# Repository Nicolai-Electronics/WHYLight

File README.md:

# WHYlight
Hardware design files for the WHYlight project.

A PoE+ powered addressable LED strip driver using an ESP32-C6.

## Features
 - 100mbit ethernet
 - PoE+ powered
 - WiFi / BLE / 802.15.4 radio
 - LoRa radio
 - Suitable for both single and dual wire addressable LEDs
 - TTL differential output for DMX

## License

Copyright 2024 Nicolai Electronics

This project is licensed [CERN-OHL-P](license.txt).

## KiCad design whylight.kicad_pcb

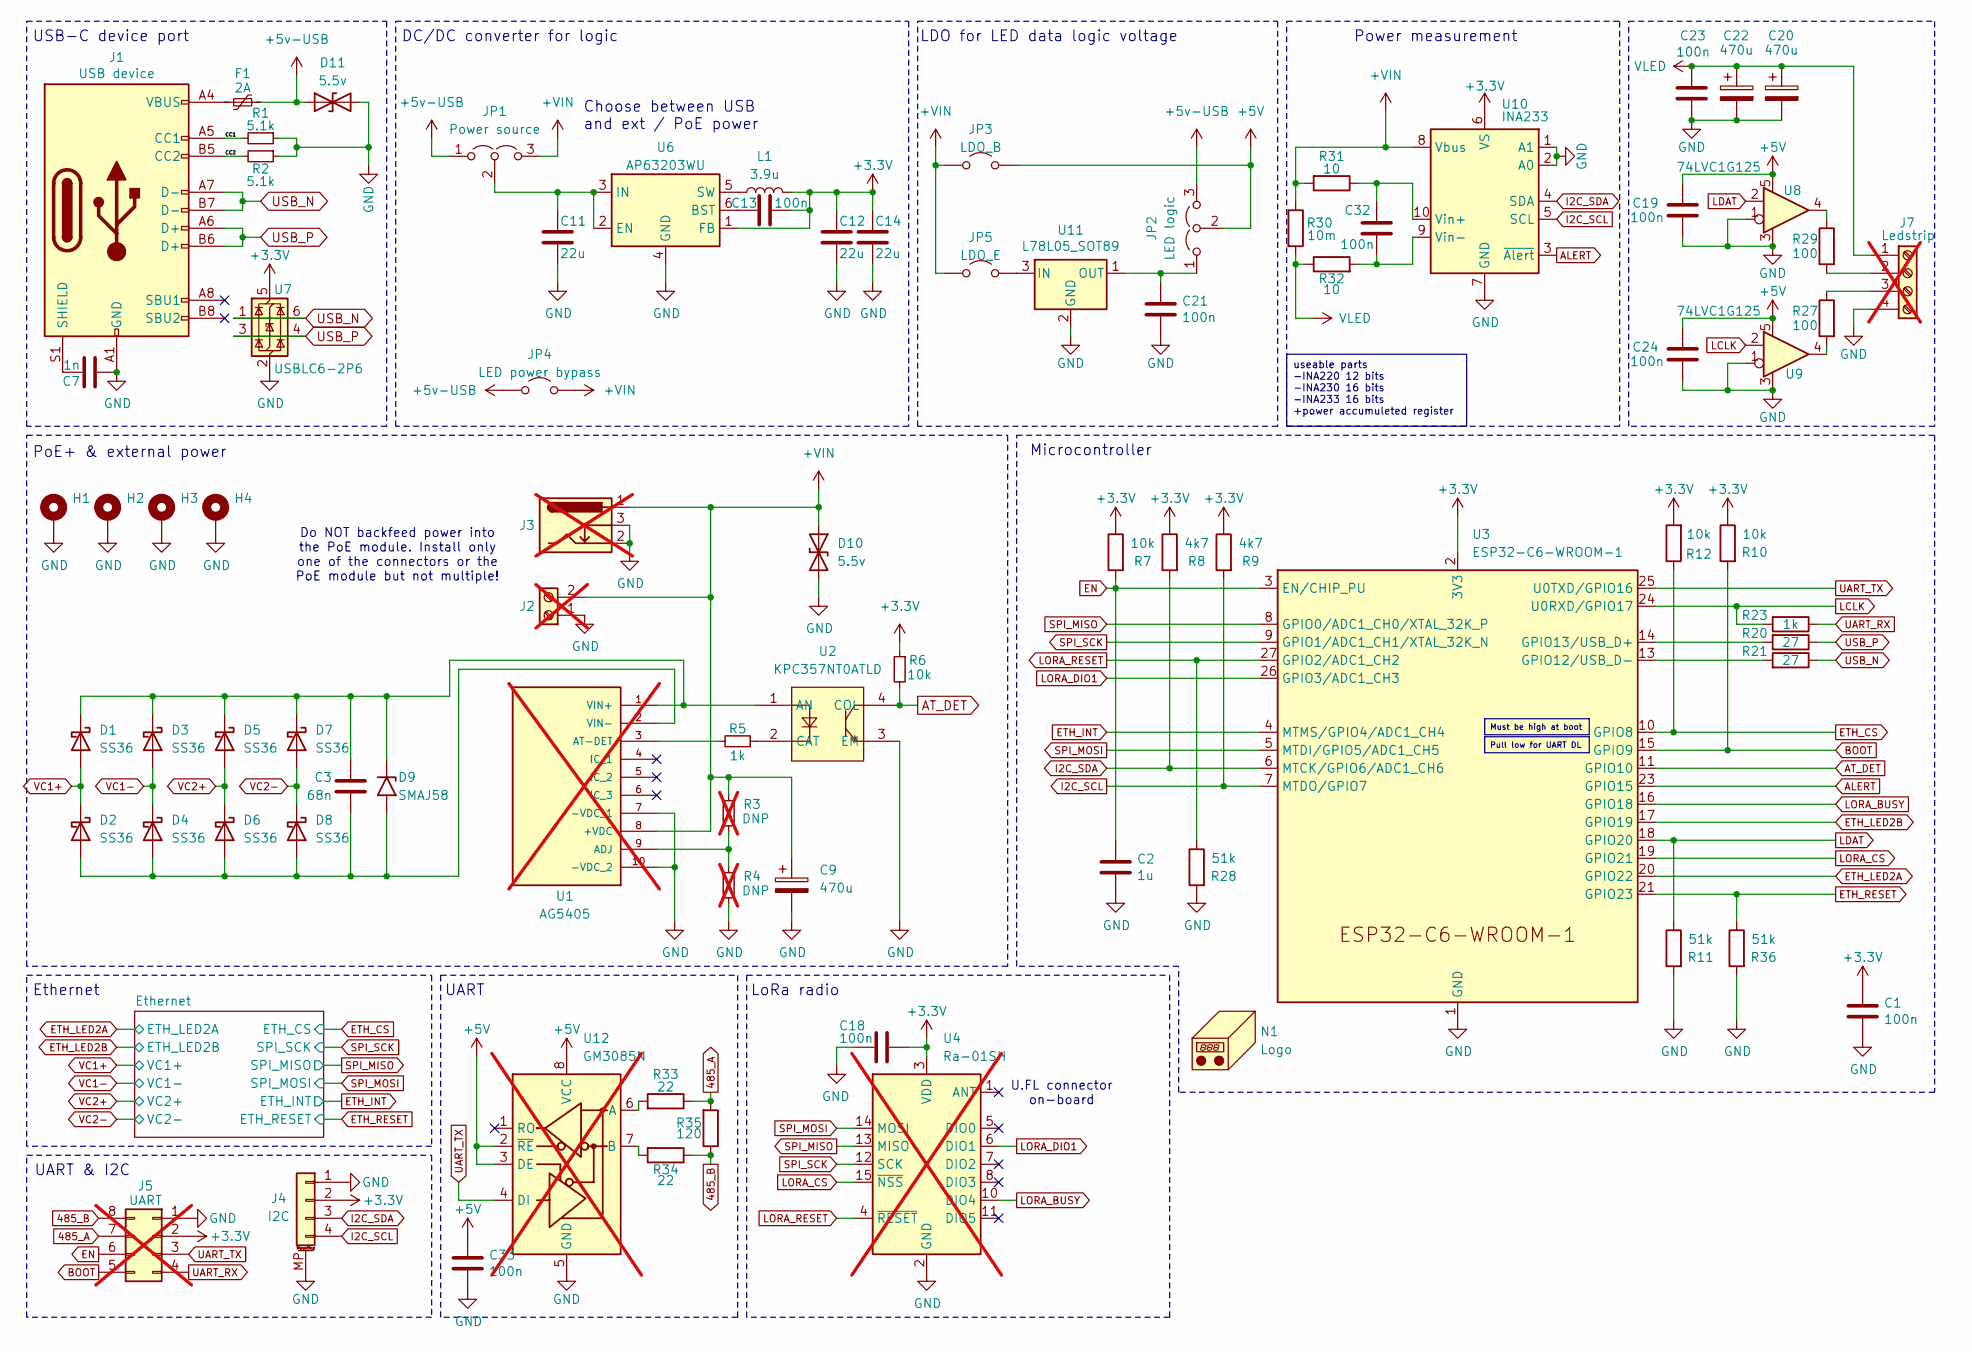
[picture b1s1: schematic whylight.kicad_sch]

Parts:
C1, C13, C18, C19, C21, C23, C24, C32, C33: 100n; C_0402_1005Metric; LCSC C394158
C2: 1u; C_0402_1005Metric; LCSC C5137485
C3: 68n; C_0402_1005Metric; LCSC C565562
C7: 1n; C_1206_3216Metric; LCSC C2173292
C9, C20, C22: 470u; CP_Elec_8x10; LCSC C2164331
C11, C12, C14: 22u; C_0805_2012Metric; LCSC C45783
D1, D2, D3, D4, D5, D6, D7, D8: SS36; D_SMA; LCSC C727061
D9: SMAJ58; D_SMA; LCSC C132935
D10, D11: 5.5v; D_SOD-323; LCSC C19224
F1: 2A; Fuse_0805_2012Metric; LCSC C70158
H1, H2, H3, H4: MountingHole_2.2mm_M2_DIN965_Pad
J1: USB device; USB_C_Receptacle_HRO_TYPE-C-31-M-12; LCSC C165948
J2: External 5v; PhoenixContact_MC_1,5_2-G-5.08_1x02_P5.08mm_Horizontal; LCSC C5188463; not fitted
J3: External 5v; BarrelJack_GCT_DCJ200-10-A_Horizontal; LCSC C381116; not fitted
J4: I2C; JST_SH_BM04B-SRSS-TB_1x04-1MP_P1.00mm_Vertical; LCSC C160390
J5: UART; PinHeader_2x04_P2.54mm_Vertical; not fitted
J7: Ledstrip; PhoenixContact_MC_1,5_4-GF-5.08_1x04_P5.08mm_Horizontal_Thr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; not fitted
JP1: Power source; SolderJumper-3_P1.3mm_Open_RoundedPad1.0x1.5mm_NumberLabels
JP2: LED logic; SolderJumper-3_P1.3mm_Open_RoundedPad1.0x1.5mm_NumberLabels
JP3: LDO_B; SolderJumper-2_P1.3mm_Open_RoundedPad1.0x1.5mm
JP4: LED power bypass; SolderJumper-2_P1.3mm_Open_RoundedPad1.0x1.5mm
JP5: LDO_E; SolderJumper-2_P1.3mm_Open_RoundedPad1.0x1.5mm
L1: 3.9u; L_Coilcraft_XAL5050-XXX; LCSC C167928
N1: Logo; logo_nicolai
R1, R2: 5.1k; R_0402_1005Metric; LCSC C25905
R3, R4: DNP; R_0402_1005Metric; not fitted
R5, R23: 1k; R_0402_1005Metric; LCSC C11702
R6, R7, R10, R12: 10k; R_0402_1005Metric; LCSC C60490
R8, R9: 4k7; R_0402_1005Metric; LCSC C25900
R11, R28, R36: 51k; R_0402_1005Metric; LCSC C25794
R20, R21: 27; R_0402_1005Metric; LCSC C25100
R27, R29: 100; R_0402_1005Metric; LCSC C25076
R30: 10m; R_1206_3216Metric; LCSC C105362
R31, R32: 10; R_0402_1005Metric; LCSC C138066
R33, R34: 22; R_0402_1005Metric; LCSC C25092
R35: 120; R_0402_1005Metric; LCSC C25079
U1: AG5405; AG5300; not fitted
U2: KPC357NT0ATLD; SOP-4_L3.9-W4.4-P2.54-LS7.0-BR; LCSC C136410
U3: ESP32-C6-WROOM-1; LCSC C5366877
U4: Ra-01SH; Ai-Thinker-Ra-01-LoRa; not fitted
U6: AP63203WU; TSOT-23-6; LCSC C780769
U7: USBLC6-2P6; SOT-666; LCSC C2827693
U8, U9: 74LVC1G125; SOT-353_SC-70-5; LCSC C12519
U10: INA233; VSSOP-10_3x3mm_P0.5mm; LCSC C2653838
U11: L78L05_SOT89; SOT-89-3; LCSC C408272
U12: GM3085N; SOIC-8_3.9x4.9mm_P1.27mm; LCSC C269865; not fitted

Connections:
485_A: J5.7, R33.1, R35.2
485_B: J5.8, R34.1, R35.1
+3.3V: C1.1, C12.1, C13.1, C14.1, C18.1, J4.2, J5.2, L1.2, R6.1, R7.1, R8.1, R9.1, R10.1, R12.2, U3.2 (3V3), U4.3 (VDD), U6.1 (FB), U7.5 (VBUS), U10.6 (VS); also elsewhere on the board
+5V: C19.2, C24.2, C33.1, JP2.2 (C), JP3.2 (B), U8.5 (VCC), U9.5 (VCC), U12.2 (~RE), U12.3 (DE), U12.8 (VCC)
+5v-USB: D11.1 (A1), F1.1, JP1.1 (A), JP2.3 (B), JP4.1 (A)
+VIN: C9.1, D10.1 (A1), J2.2, J3.1, JP1.3 (B), JP3.1 (A), JP4.2 (B), JP5.1 (A), R3.2, R30.1, R31.2, U1.8 (+VDC), U10.8 (Vbus)
/CC1: J1.A5 (CC1), R1.2
/CC2: J1.B5 (CC2), R2.2
ALERT: U3.23 (GPIO15), U10.3 (~Alert)
AT_DET: R6.2, U2.4 (COL), U3.11 (GPIO10)
BOOT: J5.5, R10.2, U3.15 (GPIO9)
EN: C2.1, J5.6, R7.2, U3.3 (EN/CHIP_PU)
ETH_CS: R12.1, U3.10 (GPIO8); also elsewhere on the board
ETH_INT: U3.4 (MTMS/GPIO4/ADC1_CH4); also elsewhere on the board
ETH_LED2A: U3.20 (GPIO22); also elsewhere on the board
ETH_LED2B: U3.17 (GPIO19); also elsewhere on the board
ETH_RESET: R36.1, U3.21 (GPIO23); also elsewhere on the board
GND: C1.2, C2.2, C7.2, C9.2, C11.2, C12.2, C14.2, C18.2, C19.1, C20.2, C21.2, C22.2, C23.2, C24.1, C33.2, D10.2 (A2), D11.2 (A2), H1.1, H2.1, H3.1, H4.1, J1.A1 (GND), J1.A12 (GND), J1.B1 (GND), J1.B12 (GND), J2.1, J3.2, J3.3, J4.1, J4.MP (MountPin), J5.1, J7.4, R1.1, R2.1, R4.1, R11.2, R28.2, R36.2, U1.7 (-VDC_1), U1.10 (-VDC_2), U2.3 (EM), U3.1 (GND), U3.12 (GPIO11), U3.28 (GND), U3.29 (GND), U4.2 (GND), U4.9 (GND), U4.16 (GND), U6.4 (GND), U7.2 (GND), U8.1, U8.3 (GND), U9.1, U9.3 (GND), U10.1 (A1), U10.2 (A0), U10.7 (GND), U11.2 (GND), U12.5 (GND); also elsewhere on the board
I2C_SCL: J4.4, R9.2, U3.7 (MTDO/GPIO7), U10.5 (SCL)
I2C_SDA: J4.3, R8.2, U3.6 (MTCK/GPIO6/ADC1_CH6), U10.4 (SDA)
LCLK: R23.2, U3.24 (U0RXD/GPIO17), U9.2
LDAT: R11.1, U3.18 (GPIO20), U8.2
LORA_BUSY: U3.16 (GPIO18), U4.10 (DIO4)
LORA_CS: U3.19 (GPIO21), U4.15 (~NSS)
LORA_DIO1: U3.26 (GPIO3/ADC1_CH3), U4.6 (DIO1)
LORA_RESET: R28.1, U3.27 (GPIO2/ADC1_CH2), U4.4 (~RESET)
unnamed: C3.1, D1.1 (K), D3.1 (K), D5.1 (K), D7.1 (K), D9.1 (A1), U1.1 (VIN+), U2.1 (AN)
unnamed: C3.2, D2.2 (A), D4.2 (A), D6.2 (A), D8.2 (A), D9.2 (A2), U1.2 (VIN-)
unnamed: F1.2, J1.A4 (VBUS), J1.A9 (VBUS), J1.B4 (VBUS), J1.B9 (VBUS)
unnamed: C7.1, J1.S1 (SHIELD)
unnamed: J7.2, R29.2
unnamed: J7.3, R27.1
unnamed: C11.1, JP1.2 (C), U6.2 (EN), U6.3 (IN)
unnamed: C21.1, JP2.1 (A), U11.1 (OUT)
unnamed: JP5.2 (B), U11.3 (IN)
unnamed: R27.2, U9.4
unnamed: R29.1, U8.4
unnamed: R3.1, R4.2, U1.9 (ADJ)
unnamed: R5.2, U1.3 (AT-DET)
unnamed: R5.1, U2.2 (CAT)
unnamed: R21.2, U3.13 (GPIO12/USB_D-)
unnamed: R20.2, U3.14 (GPIO13/USB_D+)
unnamed: C13.2, U6.6 (BST)
unnamed: L1.1, U6.5 (SW)
unnamed: C32.2, R31.1, U10.10 (Vin+)
unnamed: C32.1, R32.2, U10.9 (Vin-)
unnamed: R33.2, U12.6 (A)
unnamed: R34.2, U12.7 (B)
SPI_MISO: U3.8 (GPIO0/ADC1_CH0/XTAL_32K_P), U4.13 (MISO); also elsewhere on the board
SPI_MOSI: U3.5 (MTDI/GPIO5/ADC1_CH5), U4.14 (MOSI); also elsewhere on the board
SPI_SCK: U3.9 (GPIO1/ADC1_CH1/XTAL_32K_N), U4.12 (SCK); also elsewhere on the board
UART_RX: J5.4, R23.1
UART_TX: J5.3, U3.25 (U0TXD/GPIO16), U12.4 (DI)
USB_N: J1.A7 (D-), J1.B7 (D-), R21.1, U7.1 (I/O1), U7.6 (I/O1)
USB_P: J1.A6 (D+), J1.B6 (D+), R20.1, U7.3 (I/O2), U7.4 (I/O2)
VC1+: D1.2 (A), D2.1 (K); also elsewhere on the board
VC1-: D3.2 (A), D4.1 (K); also elsewhere on the board
VC2+: D5.2 (A), D6.1 (K); also elsewhere on the board
VC2-: D7.2 (A), D8.1 (K); also elsewhere on the board
VLED: C20.1, C22.1, C23.1, J7.1, R30.2, R32.1

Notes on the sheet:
Pull low for UART DL
Must be high at boot
useable parts -INA220 12 bits -INA230 16 bits -INA233 16 bits +power accumuleted register
Ethernet
Choose between USB and ext / PoE power
USB-C device port
Microcontroller
Power measurement
UART
DC/DC converter for logic
U.FL connector on-board
LoRa radio
PoE+ & external power
LDO for LED data logic voltage
UART & I2C
Do NOT backfeed power into the PoE module. Install only one of the connectors or the PoE module but not multiple!

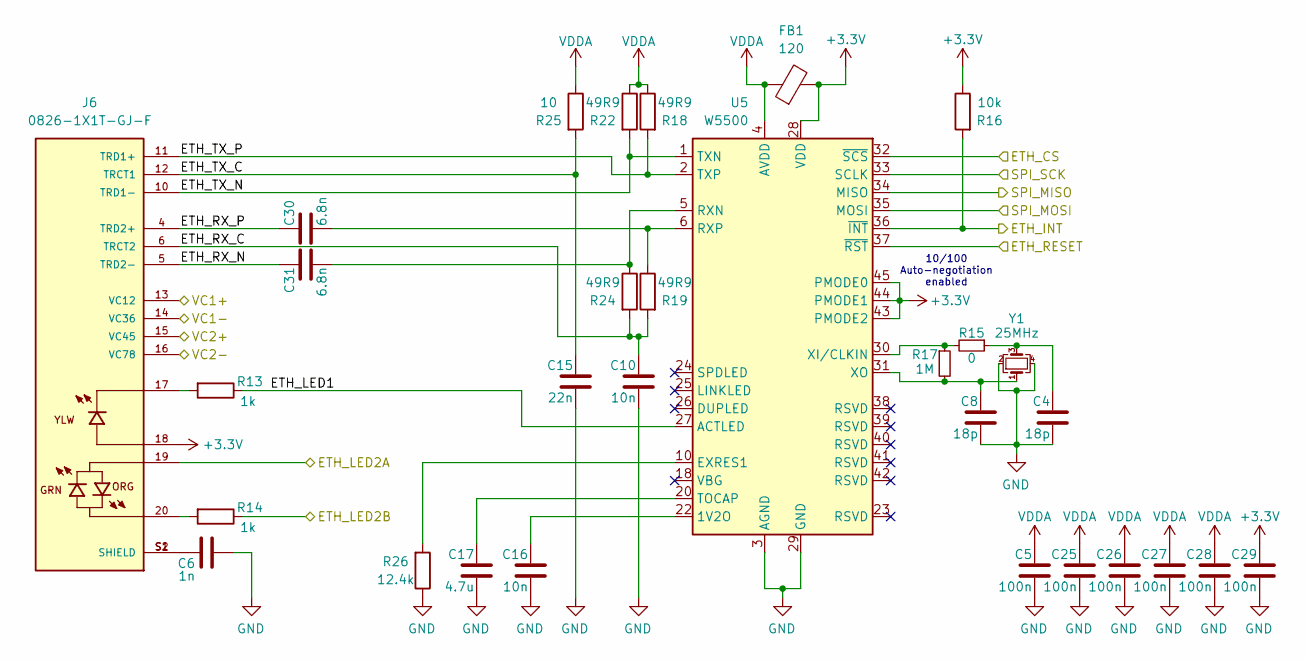
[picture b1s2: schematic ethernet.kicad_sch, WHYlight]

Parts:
C4, C8: 18p; C_0402_1005Metric; LCSC C555395
C5, C25, C26, C27, C28, C29: 100n; C_0402_1005Metric; LCSC C394158
C6: 1n; C_1206_3216Metric; LCSC C2173292
C10, C16: 10n; C_0402_1005Metric; LCSC C2875126
C15: 22n; C_0402_1005Metric; LCSC C466237
C17: 4.7u; C_0402_1005Metric; LCSC C307423
C30, C31: 6.8n; C_0402_1005Metric; LCSC C2760541
FB1: 120; L_0603_1608Metric; LCSC C709642
J6: 0826-1X1T-GJ-F; BEL_0826-1X1T-GJ-F
R13, R14: 1k; R_0402_1005Metric; LCSC C11702
R15: 0; R_0402_1005Metric; LCSC C17168
R16: 10k; R_0402_1005Metric; LCSC C60490
R17: 1M; R_0402_1005Metric; LCSC C26083
R18, R19, R22, R24: 49R9; R_0402_1005Metric; LCSC C25120
R25: 10; R_0402_1005Metric; LCSC C138066
R26: 12.4k; R_0402_1005Metric; LCSC C284314
U5: W5500; LQFP-48_7x7mm_P0.5mm; LCSC C32843
Y1: 25MHz; Crystal_SMD_3225-4Pin_3.2x2.5mm; LCSC C7424735

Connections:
+3.3V: C29.1, FB1.2, J6.18, R16.1, U5.28 (VDD), U5.43 (PMODE2), U5.44 (PMODE1), U5.45 (PMODE0); also elsewhere on the board
/Ethernet/ETH_LED1: R13.1, U5.27 (ACTLED)
/Ethernet/ETH_RX_C: C10.1, J6.6 (TRCT2), R19.2, R24.2
/Ethernet/ETH_RX_N: C31.1, J6.5 (TRD2-)
/Ethernet/ETH_RX_P: C30.1, J6.4 (TRD2+)
/Ethernet/ETH_TX_C: C15.1, J6.12 (TRCT1), R25.2
/Ethernet/ETH_TX_N: J6.10 (TRD1-), R22.2, U5.1 (TXN)
/Ethernet/ETH_TX_P: J6.11 (TRD1+), R18.2, U5.2 (TXP)
ETH_CS: U5.32 (~SCS); also elsewhere on the board
ETH_INT: R16.2, U5.36 (~INT); also elsewhere on the board
ETH_LED2A: J6.19; also elsewhere on the board
ETH_LED2B: R14.1; also elsewhere on the board
ETH_RESET: U5.37 (~RST); also elsewhere on the board
GND: C4.2, C5.2, C6.2, C8.2, C10.2, C15.2, C16.2, C17.2, C25.2, C26.2, C27.2, C28.2, C29.2, R26.1, U5.3 (AGND), U5.9 (AGND), U5.14 (AGND), U5.16 (AGND), U5.19 (AGND), U5.29 (GND), U5.48 (AGND), Y1.2, Y1.4; also elsewhere on the board
unnamed: C4.1, R15.1, Y1.3
unnamed: C6.1, J6.S1 (SHIELD), J6.S2 (SHIELD)
unnamed: J6.17, R13.2
unnamed: J6.20, R14.2
unnamed: C16.1, U5.22 (1V2O)
unnamed: R26.2, U5.10 (EXRES1)
unnamed: C31.2, R24.1, U5.5 (RXN)
unnamed: C30.2, R19.1, U5.6 (RXP)
unnamed: C17.1, U5.20 (TOCAP)
unnamed: R15.2, R17.1, U5.30 (XI/CLKIN)
unnamed: C8.1, R17.2, U5.31 (XO), Y1.1
SPI_MISO: U5.34 (MISO); also elsewhere on the board
SPI_MOSI: U5.35 (MOSI); also elsewhere on the board
SPI_SCK: U5.33 (SCLK); also elsewhere on the board
VC1+: J6.13 (VC12); also elsewhere on the board
VC1-: J6.14 (VC36); also elsewhere on the board
VC2+: J6.15 (VC45); also elsewhere on the board
VC2-: J6.16 (VC78); also elsewhere on the board
VDDA: C5.1, C25.1, C26.1, C27.1, C28.1, FB1.1, R18.1, R22.1, R25.1, U5.4 (AVDD), U5.8 (AVDD), U5.11 (AVDD), U5.15 (AVDD), U5.17 (AVDD), U5.21 (AVDD)

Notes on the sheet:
10/100 Auto-negotiation enabled

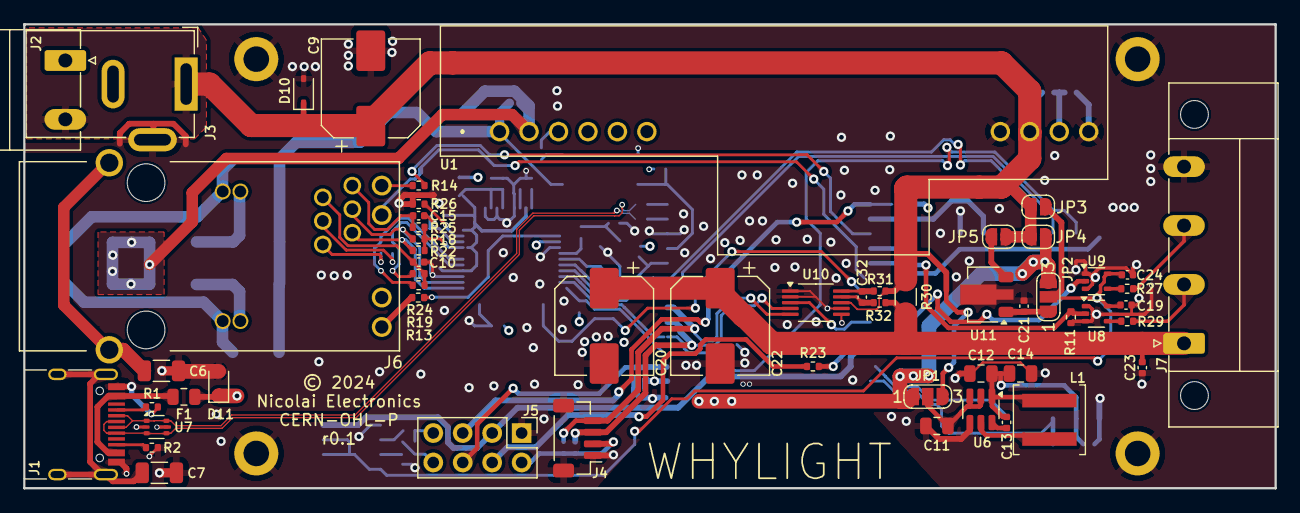
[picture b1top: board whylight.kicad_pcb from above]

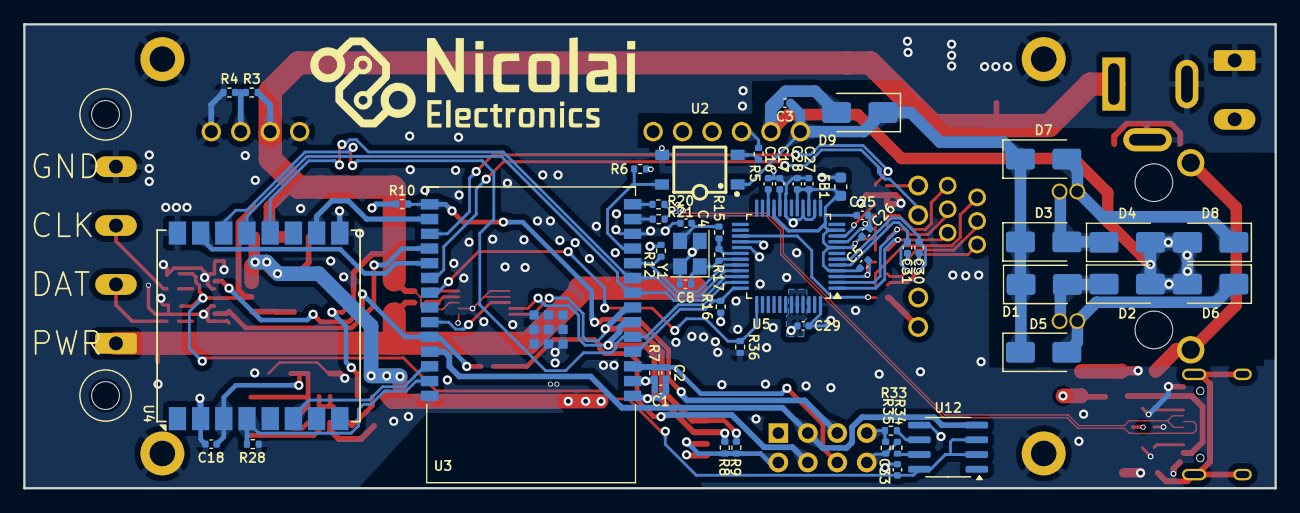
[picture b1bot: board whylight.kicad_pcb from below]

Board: 4 copper layers, 107.9 x 40.0 mm, 113 parts (53 on the bottom side), 79 nets.

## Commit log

2024-06-29 Fixes & add voltage/current monitor chip
2024-07-26 Stuff.
2024-08-05 added 3D models, added LCSC numbers, added caps in RX line ethernet as per the datasheet, change crystal and capacitors to correctly match w5500 as per the datasheet, added bead to filter analoge pow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
2024-08-15 Remove output folder
2024-08-15 Change pinout of C6 to more closely resemble the WHY2025 badge
2024-08-17 Add RS485, add mounting holes, route more stuff
2024-08-18 Finish first pass of routing
2024-08-18 Add readme
2024-08-18 Rerouted power to where there is more space, solved issue with diff pair.
2024-08-18 r0.1
2024-08-19 Release r0.1

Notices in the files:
whylight.kicad_pcb:
© 2024
CERN-OHL-P
